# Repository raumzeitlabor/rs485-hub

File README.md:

This is an RS485 hub, based on Evert Dekker's design [1]. It is modified to fit into a DIN 41612 system.

[1] http://www.evertdekker.com

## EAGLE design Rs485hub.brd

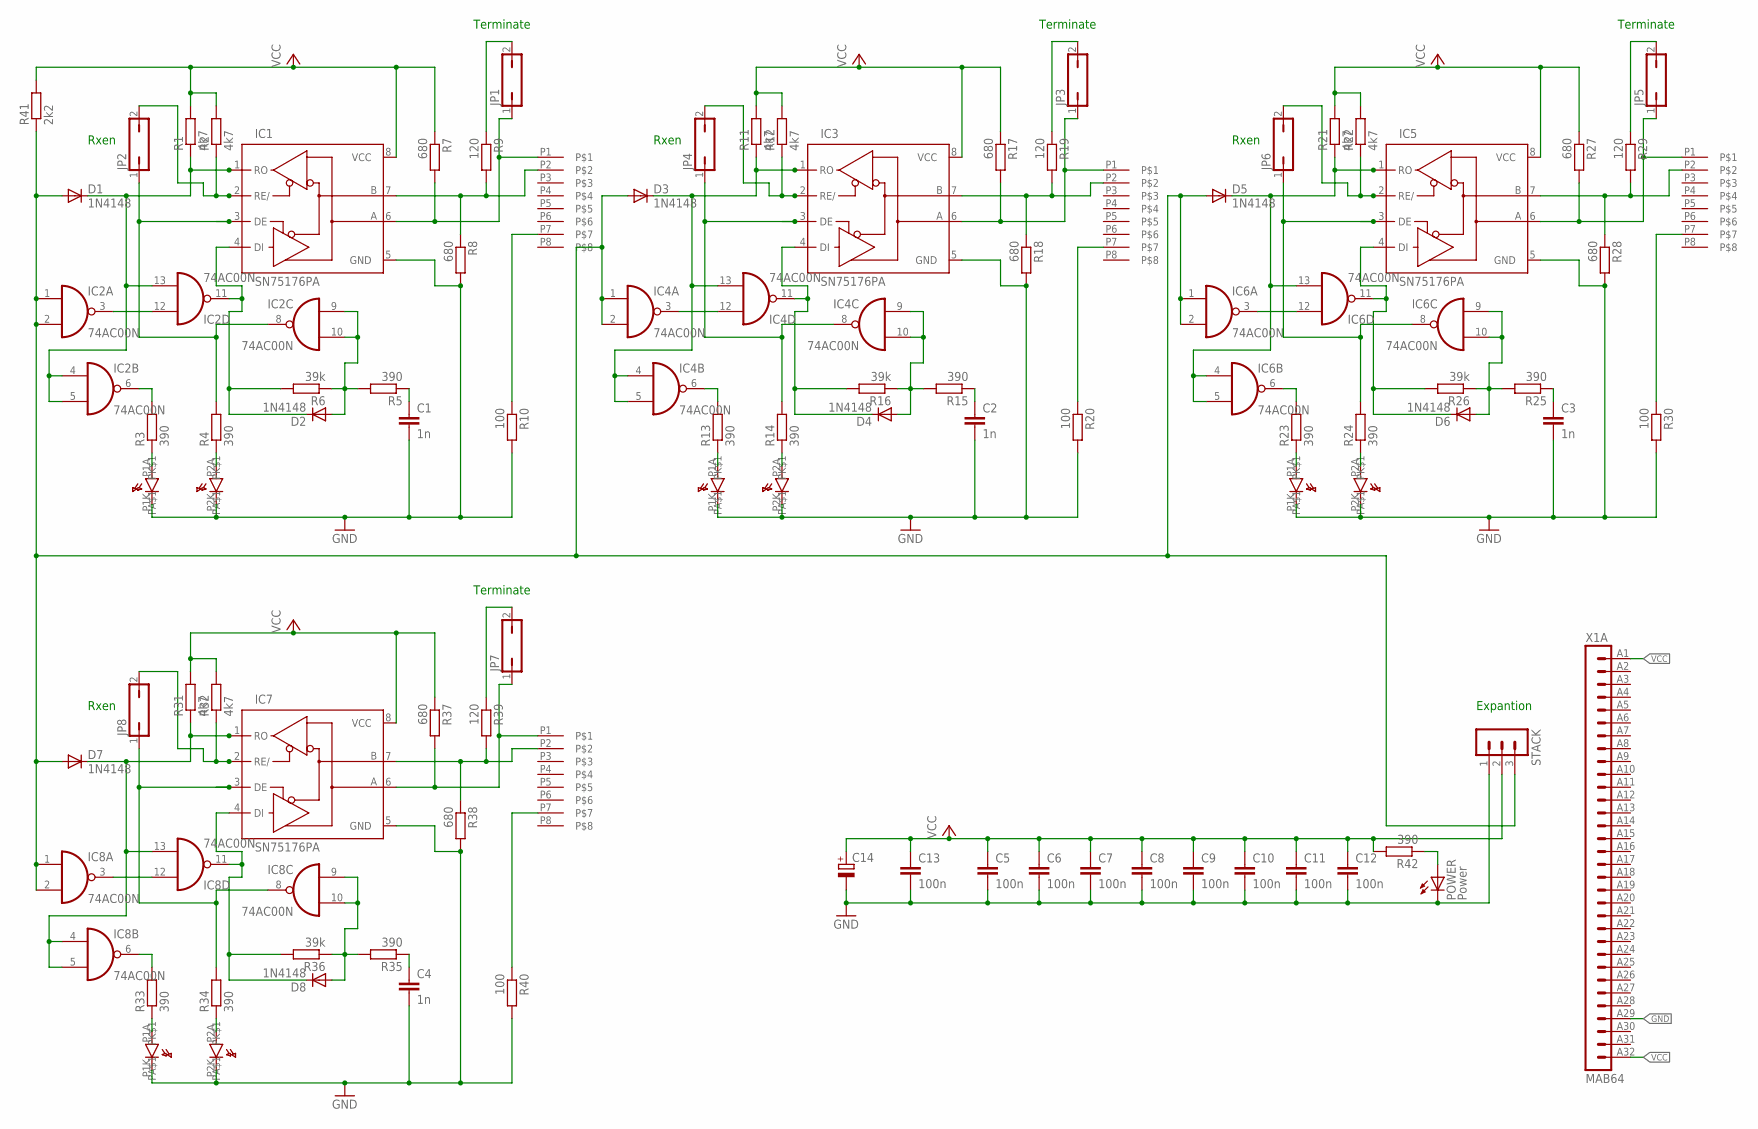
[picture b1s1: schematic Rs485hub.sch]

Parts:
C1, C2, C3, C4: 1n; C2.5-3
C5, C6, C7, C8, C9, C10, C11, C12, C13: 100n; C2.5-3
C14: CPOL-EUE5-8.5; E5-8,5
D1, D2, D3, D4, D5, D6, D7, D8: 1N4148; DO35-10
IC1, IC3, IC5, IC7: SN75176PA; DIL08
IC2, IC4, IC6, IC8: 74AC00N; DIL14
JP1, JP2, JP3, JP4, JP5, JP6, JP7, JP8: JP1Q; JP1
POWER: Power; LED3MM
R1, R2, R11, R12, R21, R22, R31, R32: 4k7; 0309/10
R3, R4, R5, R13, R14, R15, R23, R24, R25, R33, R34, R35, R42: 390; 0309/10
R6, R16, R26, R36: 39k; 0309/10
R7, R8, R17, R18, R27, R28, R37, R38: 680; 0309/10
R9, R19, R29, R39: 120; 0309/10
R10, R20, R30, R40: 100; 0309/10
R41: 2k2; 0309/10
STACK: MA03-1
U$2, U$3, U$4, U$5: RJHS508; P-RJHS-538X
X1: MAB64

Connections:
DATABUS: D1.A, D3.A, D5.A, D7.A, IC2.1 (I0), IC2.2 (I1), IC4.1 (I0), IC4.2 (I1), IC6.1 (I0), IC6.2 (I1), IC8.1 (I0), IC8.2 (I1), R41.1, STACK.3
GND: C1.2, C2.2, C3.2, C4.2, C5.2, C6.2, C7.2, C8.2, C9.2, C10.2, C11.2, C12.2, C13.2, C14.-, IC1.5 (GND), IC2.7 (GND), IC3.5 (GND), IC4.7 (GND), IC5.5 (GND), IC6.7 (GND), IC7.5 (GND), IC8.7 (GND), POWER.K (C), R8.2, R10.2, R18.2, R20.2, R28.2, R30.2, R38.2, R40.2, STACK.1, U$2.P1K (PK$1), U$2.P2K (PK$1), U$3.P1K (PK$1), U$3.P2K (PK$1), U$4.P1K (PK$1), U$4.P2K (PK$1), U$5.P1K (PK$1), U$5.P2K (PK$1), X1.A29 (29)
unnamed: R4.1, U$2.P2A (PA$1)
unnamed: R3.1, U$2.P1A (PA$1)
unnamed: R10.1, U$2.P7
unnamed: IC1.7 (B), R8.1, R9.2, U$2.P2
unnamed: JP1.2, R9.1
unnamed: R14.1, U$3.P2A (PA$1)
unnamed: D1.C, IC1.1 (RO), IC2.4 (I0), IC2.5 (I1), IC2.13 (I1), R1.1
unnamed: IC2.3 (O), IC2.12 (I0)
unnamed: IC1.6 (A), JP1.1, R7.2, U$2.P1
unnamed: IC2.6 (O), R3.2
unnamed: IC1.3 (DE), IC2.8 (O), JP2.1, R4.2
unnamed: IC1.2 (RE/), JP2.2, R2.1
unnamed: D2.A, IC2.9 (I0), IC2.10 (I1), R5.2, R6.1
unnamed: D2.C, IC1.4 (DI), IC2.11 (O), R6.2
unnamed: C1.1, R5.1
unnamed: R13.1, U$3.P1A (PA$1)
unnamed: IC3.7 (B), R18.1, R19.2, U$3.P2
unnamed: JP3.2, R19.1
unnamed: IC3.6 (A), JP3.1, R17.2, U$3.P1
unnamed: IC7.6 (A), JP7.1, R37.2, U$5.P1
unnamed: D3.C, IC3.1 (RO), IC4.4 (I0), IC4.5 (I1), IC4.13 (I1), R11.1
unnamed: IC4.3 (O), IC4.12 (I0)
unnamed: IC4.6 (O), R13.2
unnamed: IC3.3 (DE), IC4.8 (O), JP4.1, R14.2
unnamed: D4.A, IC4.9 (I0), IC4.10 (I1), R15.2, R16.1
unnamed: D4.C, IC3.4 (DI), IC4.11 (O), R16.2
unnamed: C2.1, R15.1
unnamed: IC3.2 (RE/), JP4.2, R12.1
unnamed: R20.1, U$3.P7
unnamed: R24.1, U$4.P2A (PA$1)
unnamed: R23.1, U$4.P1A (PA$1)
unnamed: IC5.7 (B), R28.1, R29.2, U$4.P2
unnamed: JP5.2, R29.1
unnamed: IC5.6 (A), JP5.1, R27.2, U$4.P1
unnamed: POWER.A, R42.1
unnamed: D5.C, IC5.1 (RO), IC6.4 (I0), IC6.5 (I1), IC6.13 (I1), R21.1
unnamed: IC6.3 (O), IC6.12 (I0)
unnamed: IC6.6 (O), R23.2
unnamed: IC5.3 (DE), IC6.8 (O), JP6.1, R24.2
unnamed: D6.A, IC6.9 (I0), IC6.10 (I1), R25.2, R26.1
unnamed: D6.C, IC5.4 (DI), IC6.11 (O), R26.2
unnamed: C3.1, R25.1
unnamed: IC5.2 (RE/), JP6.2, R22.1
unnamed: R30.1, U$4.P7
unnamed: R34.1, U$5.P2A (PA$1)
unnamed: R33.1, U$5.P1A (PA$1)
unnamed: IC7.7 (B), R38.1, R39.2, U$5.P2
unnamed: JP7.2, R39.1
unnamed: D7.C, IC7.1 (RO), IC8.4 (I0), IC8.5 (I1), IC8.13 (I1), R31.1
unnamed: IC8.3 (O), IC8.12 (I0)
unnamed: IC8.6 (O), R33.2
unnamed: IC7.3 (DE), IC8.8 (O), JP8.1, R34.2
unnamed: D8.A, IC8.9 (I0), IC8.10 (I1), R35.2, R36.1
unnamed: D8.C, IC7.4 (DI), IC8.11 (O), R36.2
unnamed: C4.1, R35.1
unnamed: IC7.2 (RE/), JP8.2, R32.1
unnamed: R40.1, U$5.P7
VCC: C5.1, C6.1, C7.1, C8.1, C9.1, C10.1, C11.1, C12.1, C13.1, C14.+, IC1.8 (VCC), IC2.14 (VCC), IC3.8 (VCC), IC4.14 (VCC), IC5.8 (VCC), IC6.14 (VCC), IC7.8 (VCC), IC8.14 (VCC), R1.2, R2.2, R7.1, R11.2, R12.2, R17.1, R21.2, R22.2, R27.1, R31.2, R32.2, R37.1, R41.2, R42.2, STACK.2, X1.A1 (1), X1.A32 (32)

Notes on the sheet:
Terminate
Rxen
Expantion

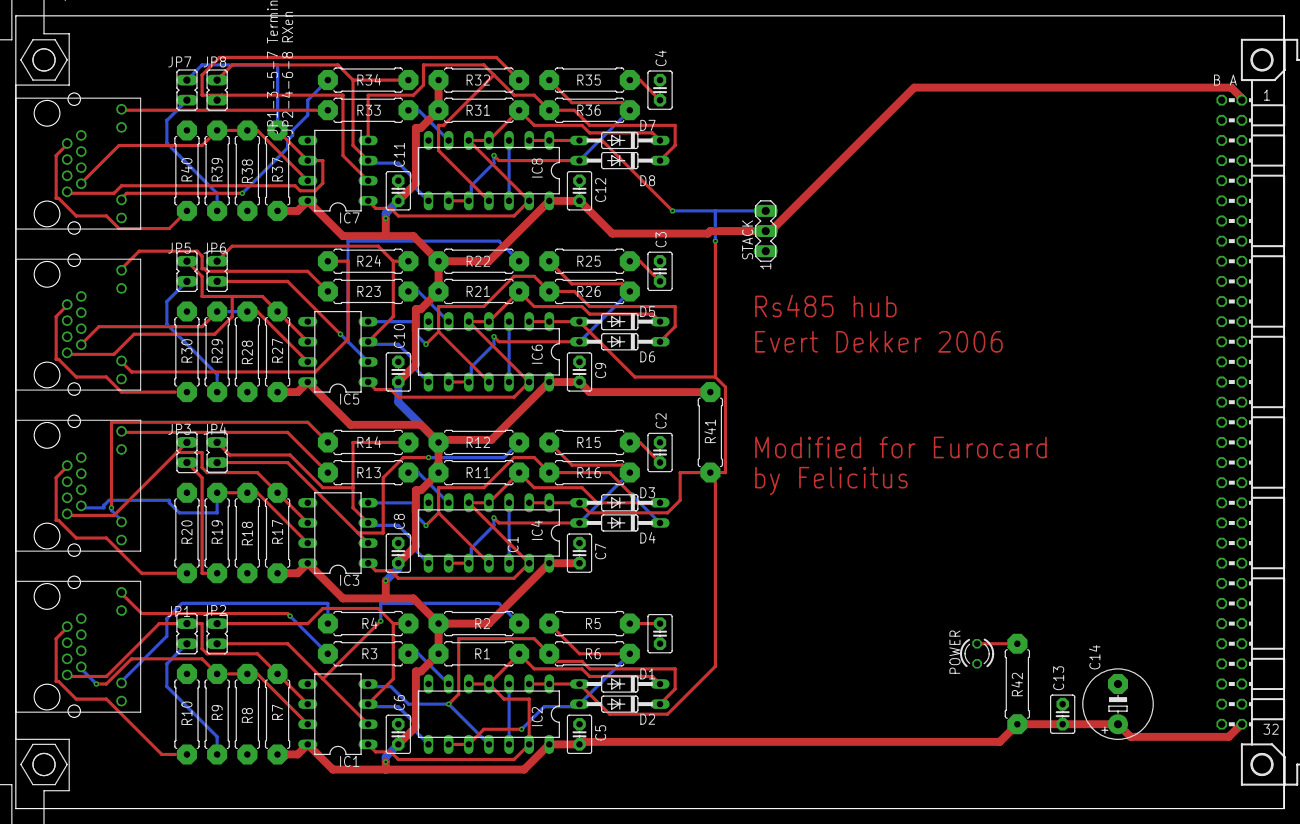
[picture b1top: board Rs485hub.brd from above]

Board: 2 copper layers, 160.0 x 100.0 mm, 88 parts (0 on the bottom side), 60 nets.

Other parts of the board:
U$6: EK-FP

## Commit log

2013-11-22 Further mods for the 19" rack at RaumZeitLabor, still needs routing
2013-11-29 Added routing ;)
2013-11-29 Added nice pics
